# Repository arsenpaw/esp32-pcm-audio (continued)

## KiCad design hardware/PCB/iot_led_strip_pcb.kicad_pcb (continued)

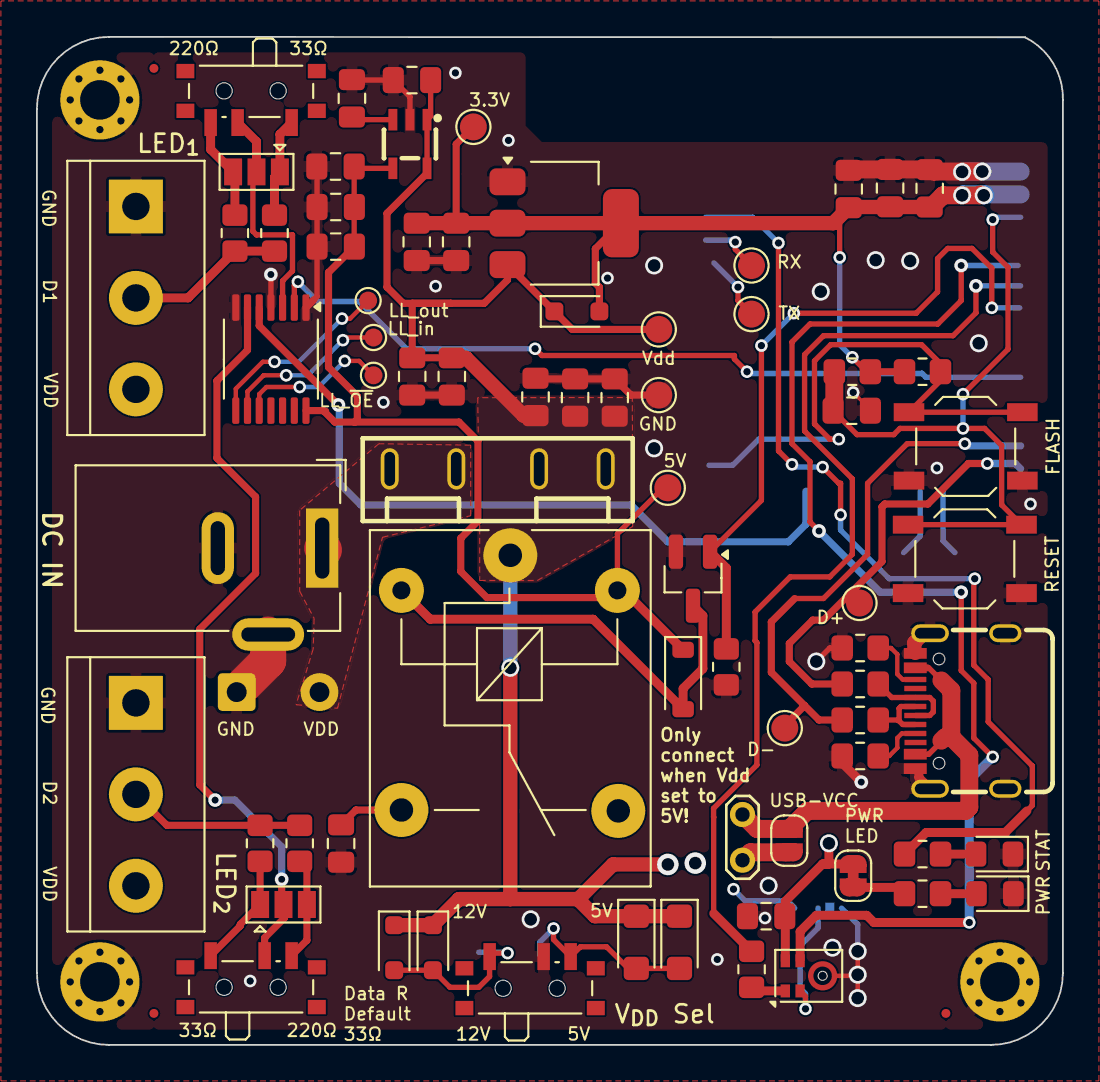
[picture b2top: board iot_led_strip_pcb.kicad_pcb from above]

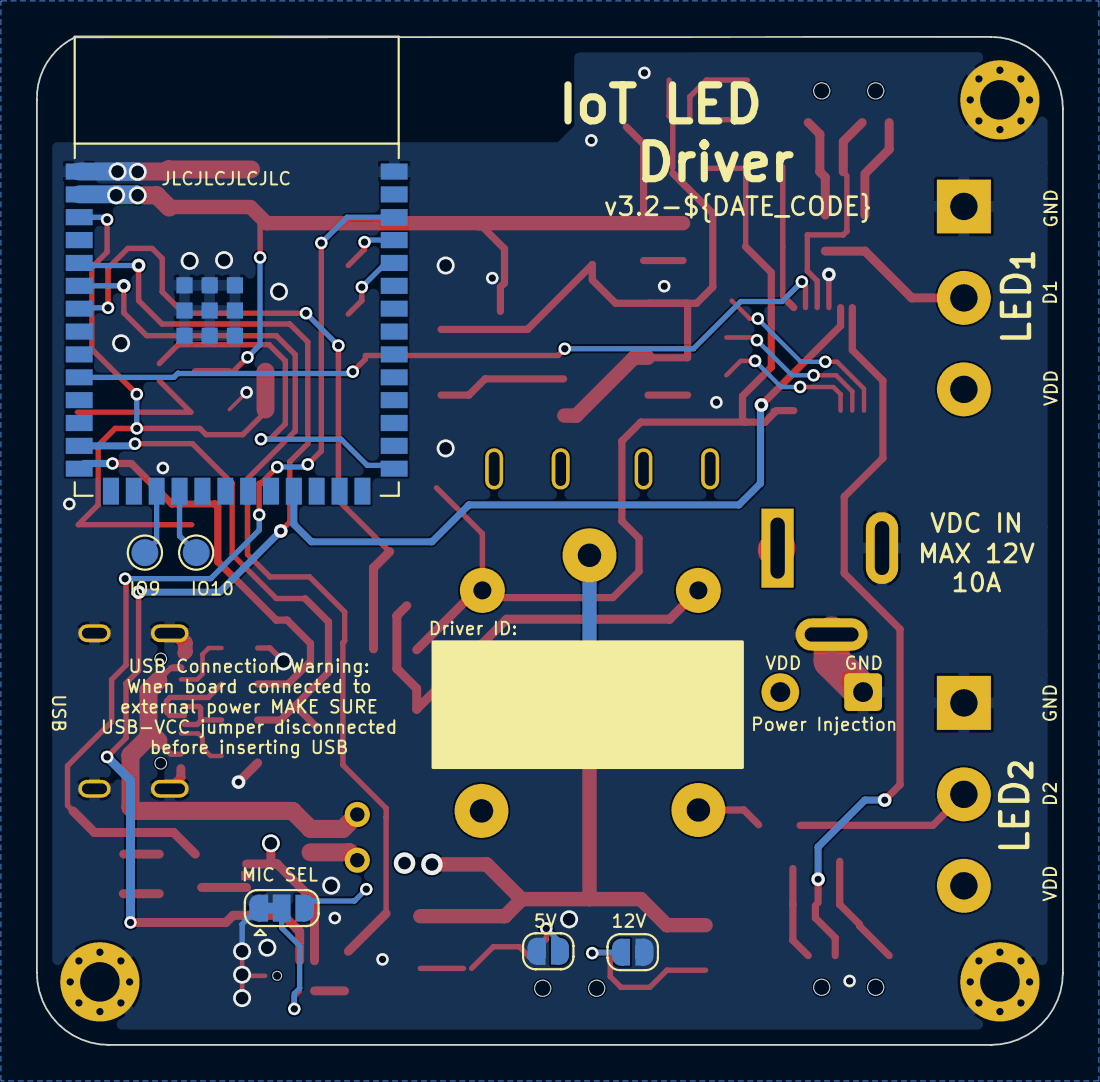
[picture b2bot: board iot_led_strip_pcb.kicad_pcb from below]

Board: 4 copper layers, 57.0 x 56.0 mm, 85 parts (6 on the bottom side), 45 nets.

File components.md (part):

# Components

This is everything you need to build **one** finished board, `hardware/PCB/iot_led_strip_pcb`,
including the parts that aren't soldered onto it. Part numbers are LCSC numbers, and each one
links to its LCSC page. Prices are in USD at qty 1.
- **Checked live on lcsc.com (2026-11-17/18):** U3, J3, and LCSC's lack of stock for MK1 and J4.
- **Everything else:** from the JLCPCB/LCSC parts snapshot dated 2026-11-14.

See [shop.md](shop.md) for why each part was chosen and for ways to cut cost.

## Decide first

The board has three spots where you either fit a switch to choose later or set the choice once
with a solder bridge. These choices change what you buy.

| Choice | Switchable (buy more) | Fixed (buy less) |
|---|---|---|
| **Strip voltage** (overvoltage protection) | Fit **SW5** ("Vdd Sel") and **both** TVS pairs, D1/D2 (5 V) and D7/D8 (12 V). | Skip SW5. Fit only **D1/D2** and bridge **JP4** for 5 V strips, or only **D7/D8** and bridge **JP8** for 12 V strips. JP4 and JP8 are on the back. |
| **Data-line resistor** per strip | Fit **SW3** and **SW4** and **all four** resistors: R7/R17 (33 Ω) and R16/R18 (220 Ω). | Skip SW3/SW4. Bridge JP5/JP6 toward the resistor you want. Fit only R7/R17 (33 Ω), when data and GND share a cable, or only R16/R18 (220 Ω), when they're separate wires. |
| **USB powers the board** | Fit the **JP1 header and jumper cap**, so you can pull the cap before connecting USB while external power is on. The board's back silkscreen warns about this. | Solder-bridge **JP3** instead. USB and the barrel jack are then always joined, so never plug in both. |

The tables below list the **switchable** version, which is everything.

## Parts soldered on the board

### Modules and ICs

| Ref | Qty | Part | What it does | LCSC | Unit $ |
|---|---|---|---|---|---|
| U3 | 1 | ESP32-S3-WROOM-1-N4 | Wi-Fi MCU that runs WLED. Use the S3, not the S2, so the PDM mic works. | [C2913197](https://www.lcsc.com/product-detail/C2913197.html) | 4.31 |
| MK1 | 1 | Knowles SPH0641LM4H-1 | PDM MEMS microphone for sound-reactive effects. **LCSC has none in stock.** Order it through JLCPCB assembly or from DigiKey/Mouser. SPH0641LU4H-1 also fits. | [C497724](https://www.lcsc.com/product-detail/C497724.html) | 1.68 |
| U4 | 1 | 74HCT125T14-13, TSSOP-14 | Shifts the 3.3 V data signal up to 5 V for the strips. | [C842453](https://www.lcsc.com/product-detail/C842453.html) | 0.24 |
| U1 | 1 | AMS1117-3.3, SOT-223 | 3.3 V regulator for the ESP32. | [C6186](https://www.lcsc.com/product-detail/C6186.html) | 0.21 |
| U2 | 1 | TAR5S50, SSOP-5 | 5 V regulator for the level shifter and relay coil, needed when running 12 V strips. | [C146354](https://www.lcsc.com/product-detail/C146354.html) | 0.36 |
| Q1 | 1 | AO3400A N-MOSFET, SOT-23 | Relay driver. | [C20917](https://www.lcsc.com/product-detail/C20917.html) | 0.09 |

### Connectors, relay and fuse holder

| Ref | Qty | Part | What it does | LCSC | Unit $ |
|---|---|---|---|---|---|
| J3 | 1 | G-Switch GT-USB-7010ASV, USB-C 16P | Programming and USB power. LCSC sells a minimum of 5. | [C2988369](https://www.lcsc.com/product-detail/C2988369.html) | 0.09 |
| J4 | 1 | **Würth 694106301002** DC barrel jack | Main power input. **Buy the genuine Würth part from DigiKey/Mouser.** LCSC only has DC005 lookalikes, rated 0.5–2 A, which may not fit this footprint. | — | — |
| J1, J2 | 2 | 3-pin 5.08 mm screw terminal | LED strip outputs (5V / DATA / GND). | [C500022](https://www.lcsc.com/product-detail/C500022.html) | 0.15 |
| K2 | 1 | Songle SRD-05VDC-SL-C relay | Lets WLED switch the strip power on and off. | [C35449](https://www.lcsc.com/product-detail/C35449.html) | 0.44 |
| F2 | 1 | XF-505P blade fuse holder, through-hole | Holds the main fuse, F3. | [C843270](https://www.lcsc.com/product-detail/C843270.html) | 0.11 |
| JP1 | 1 | 1×2 pin header, 2.54 mm | USB power link (see "Decide first"). | [C358684](https://www.lcsc.com/product-detail/C358684.html) | 0.01 |
| JP1 | 1 | Jumper cap, 2.54 mm | Fits the header above. | [C18185737](https://www.lcsc.com/product-detail/C18185737.html) | 0.01 |

### Switches

| Ref | Qty | Part | What it does | LCSC | Unit $ |
|---|---|---|---|---|---|
| SW1, SW2 | 2 | Tactile switch, 5.1 mm | RESET and FLASH (boot) buttons. | [C318884](https://www.lcsc.com/product-detail/C318884.html) | 0.02 |
| SW3, SW4 | 2 | SK-3296S-01-L1 slide switch | Picks the 33 Ω or 220 Ω data resistor for each strip. Optional. | [C319020](https://www.lcsc.com/product-detail/C319020.html) | 0.08 |
| SW5 | 1 | SK-3296S-01-L1 slide switch | Picks 5 V or 12 V strip protection. Optional. | [C319020](https://www.lcsc.com/product-detail/C319020.html) | 0.08 |

### Diodes and LEDs

| Ref | Qty | Part | What it does | LCSC | Unit $ |
|---|---|---|---|---|---|
| D1, D2 | 2 | SMF5.0A TVS, SMF | Overvoltage protection for **5 V** strips. Only 130 in stock; the fallback is [C1972946](https://www.lcsc.com/product-detail/C1972946.html) ($0.16). | [C20883238](https://www.lcsc.com/product-detail/C20883238.html) | 0.02 |
| D7, D8 | 2 | PTVSHC3D12VU TVS, SOD-323 | Overvoltage protection for **12 V** strips. | [C169336](https://www.lcsc.com/product-detail/C169336.html) | 0.04 |
| D3 | 1 | 1N5819WS Schottky, SOD-323 | Protects the 3.3 V regulator if its input drops below its output. | [C191023](https://www.lcsc.com/product-detail/C191023.html) | 0.01 |
| D6 | 1 | 1N4148W, SOD-123 | Flyback diode across the relay coil. | [C81598](https://www.lcsc.com/product-detail/C81598.html) | 0.01 |
| D4 | 1 | Green LED, 0805 | "STAT" status LED on GPIO2. | [C2297](https://www.lcsc.com/product-detail/C2297.html) | 0.02 |
| D5 | 1 | Red LED, 0805 | "PWR" power LED. You can disable it with JP2. | [C84256](https://www.lcsc.com/product-detail/C84256.html) | 0.01 |

### Capacitors (all 0805)

| Ref | Qty | Part | LCSC | Unit $ |
|---|---|---|---|---|
| C1-C3, C5, C8, C13, C15-C17 | 9 | 10 µF 25 V X5R | [C15850](https://www.lcsc.com/product-detail/C15850.html) | 0.07 |
| C4, C6, C7, C9-C12, C14, C18 | 9 | 100 nF 50 V X7R | [C49678](https://www.lcsc.com/product-detail/C49678.html) | 0.02 |

### Resistors (all 0805)

| Ref | Qty | Value | What it does | LCSC | Unit $ |
|---|---|---|---|---|---|
| R1, R4, R5 | 3 | 10 kΩ | Pull-ups and pull-downs. | [C17414](https://www.lcsc.com/product-detail/C17414.html) | 0.003 |
| R8, R9 | 2 | 5.1 kΩ | USB-C CC pins, so a USB-C charger supplies 5 V. | [C27834](https://www.lcsc.com/product-detail/C27834.html) | 0.006 |
| R12, R14 | 2 | 1 kΩ | LED current limiting. | [C17513](https://www.lcsc.com/product-detail/C17513.html) | 0.004 |
| R3, R10 | 2 | 27 Ω | USB data lines. | [C17594](https://www.lcsc.com/product-detail/C17594.html) | 0.003 |
| R6 | 1 | 100 Ω | Mic data line. | [C17408](https://www.lcsc.com/product-detail/C17408.html) | 0.004 |
| R7, R17 | 2 | 33 Ω | Strip data resistor, when data and GND share a cable. | [C17634](https://www.lcsc.com/product-detail/C17634.html) | 0.005 |
| R16, R18 | 2 | 220 Ω | Strip data resistor, when data and power run as separate wires. | [C17557](https://www.lcsc.com/product-detail/C17557.html) | 0.006 |

Not bought: JP2–JP8 are solder jumpers, and the TP test points, H mounting holes, FID fiducials
and J7 (power-injection wire pads) are bare copper.

## Parts not soldered on the board

| Item | Qty | Notes |
|---|---|---|
| **PCB** | 1 | `hardware/PCB/iot_led_strip_pcb.kicad_pcb`, about 57 × 56 mm. Order from JLCPCB or similar. |
| **F3 blade fuse** | 1 | A low-profile blade fuse to fit the XF-505P holder. Pick it for your strip current; the board is labelled max 10 A, and the holder is rated 15 A. |
| **Power supply** | 1 | 5 V or 12 V to match your strips, with a 5.5 × 2.1 mm barrel plug, sized for the strip current. A USB-C charger works for short strips. |
| **USB-C cable** | 1 | For flashing WLED. |
| **LED strips** | 1–2 | WS2812B (5 V) or WS2811 (12 V), connected to J1/J2 as 5V / DATA / GND. |
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
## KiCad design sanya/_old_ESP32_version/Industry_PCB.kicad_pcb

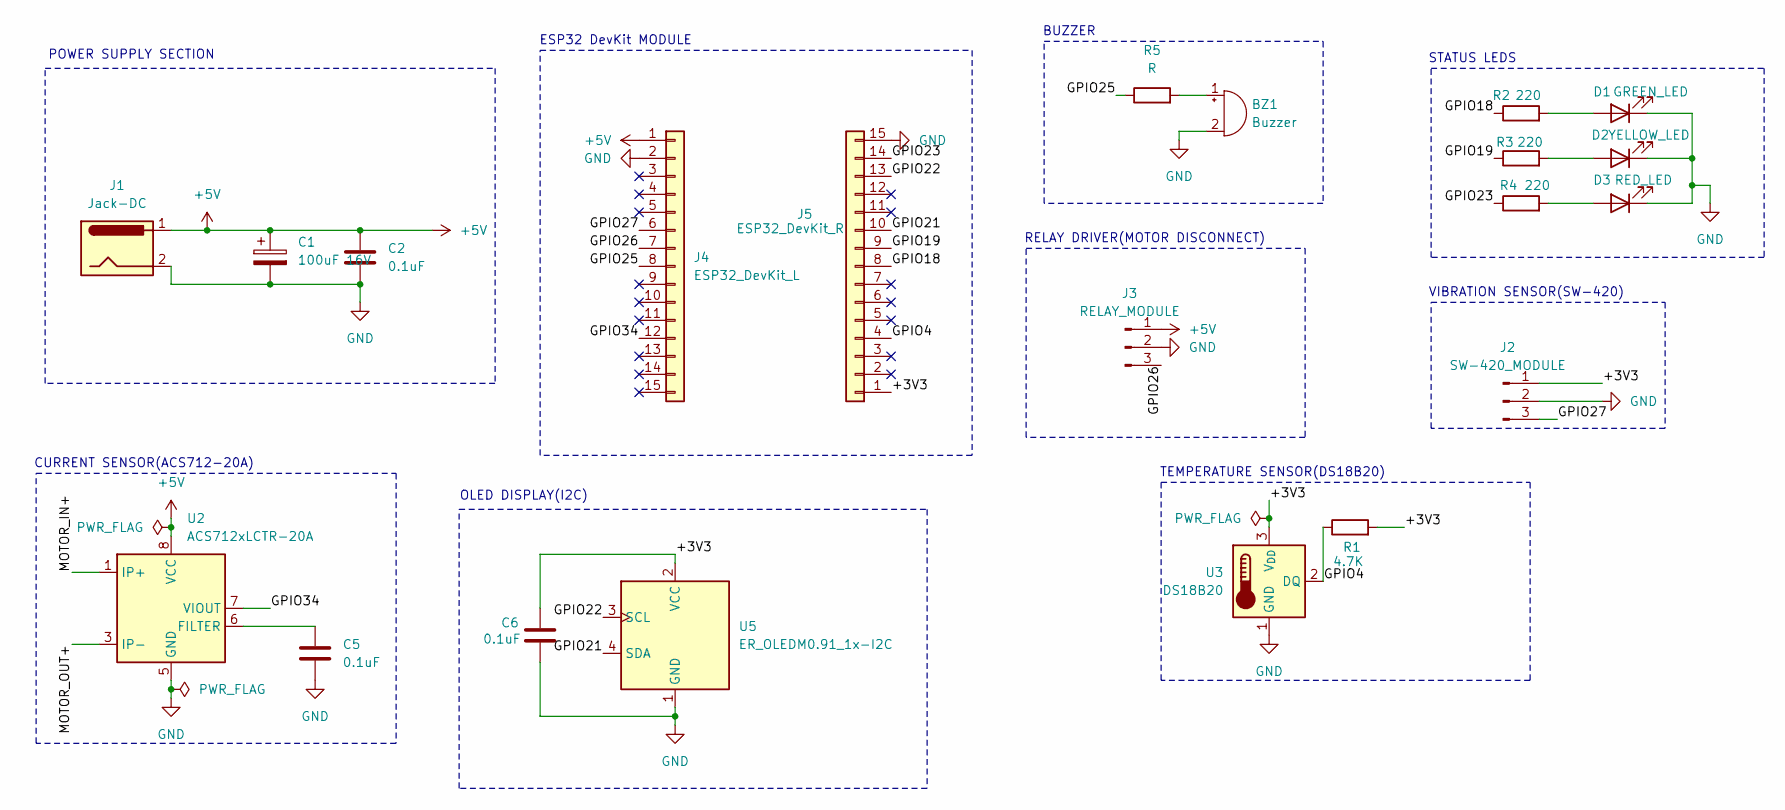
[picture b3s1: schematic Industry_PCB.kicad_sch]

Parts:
BZ1: Buzzer; Buzzer_12x9.5RM7.6
C1: 100uF 16V; CP_Radial_D6.3mm_P2.50mm
C2, C5, C6: 0.1uF; C_Disc_D5.1mm_W3.2mm_P5.00mm
D1: GREEN_LED; LED_D5.0mm
D2: YELLOW_LED; LED_D5.0mm
D3: RED_LED; LED_D5.0mm
J1: Jack-DC; BarrelJack_Horizontal
J2: SW-420_MODULE; PinHeader_1x03_P2.54mm_Vertical
J3: RELAY_MODULE; PinHeader_1x03_P2.54mm_Vertical
J4: ESP32_DevKit_L; PinHeader_1x15_P2.54mm_Vertical
J5: ESP32_DevKit_R; PinHeader_1x15_P2.54mm_Vertical
R1: 4.7K; R_Axial_DIN0207_L6.3mm_D2.5mm_P7.62mm_Horizontal
R2, R3, R4: 220; R_Axial_DIN0207_L6.3mm_D2.5mm_P7.62mm_Horizontal
R5: R; R_Axial_DIN0207_L6.3mm_D2.5mm_P7.62mm_Horizontal
U2: ACS712xLCTR-20A; SOIC-8_3.9x4.9mm_P1.27mm
U3: DS18B20; TO-92_Inline
U5: ER_OLEDM0.91_1x-I2C

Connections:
+5V: C1.1, C2.1, J1.1, J3.1, J4.1, U2.8 (VCC)
/+3V3: C6.1, J2.1, J5.1, R1.2, U3.3 (V_{DD}), U5.2 (VCC)
/GPIO4: J5.4, R1.1, U3.2 (DQ)
/GPIO18: J5.8, R2.1
/GPIO19: J5.9, R3.1
/GPIO21: J5.10, U5.4 (SDA)
/GPIO22: J5.13, U5.3 (SCL)
/GPIO23: J5.14, R4.1
/GPIO25: J4.8, R5.1
/GPIO26: J3.3, J4.7
/GPIO27: J2.3, J4.6
/GPIO34: J4.12, U2.7 (VIOUT)
/MOTOR_IN+: U2.1 (IP+), U2.2 (IP+)
/MOTOR_OUT+: U2.3 (IP-), U2.4 (IP-)
GND: BZ1.2 (-), C1.2, C2.2, C5.2, C6.2, D1.1 (K), D2.1 (K), D3.1 (K), J1.2, J2.2, J3.2, J4.2, J5.15, U2.5 (GND), U3.1 (GND), U5.1 (GND)
unnamed: BZ1.1 (+), R5.2
unnamed: D1.2 (A), R2.2
unnamed: D2.2 (A), R3.2
unnamed: D3.2 (A), R4.2
unnamed: C5.1, U2.6 (FILTER)

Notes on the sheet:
RELAY DRIVER(MOTOR DISCONNECT)
VIBRATION SENSOR(SW-420)
STATUS LEDS
ESP32 DevKit MODULE
TEMPERATURE SENSOR(DS18B20)
POWER SUPPLY SECTION
OLED DISPLAY(I2C)
CURRENT SENSOR(ACS712-20A)
BUZZER

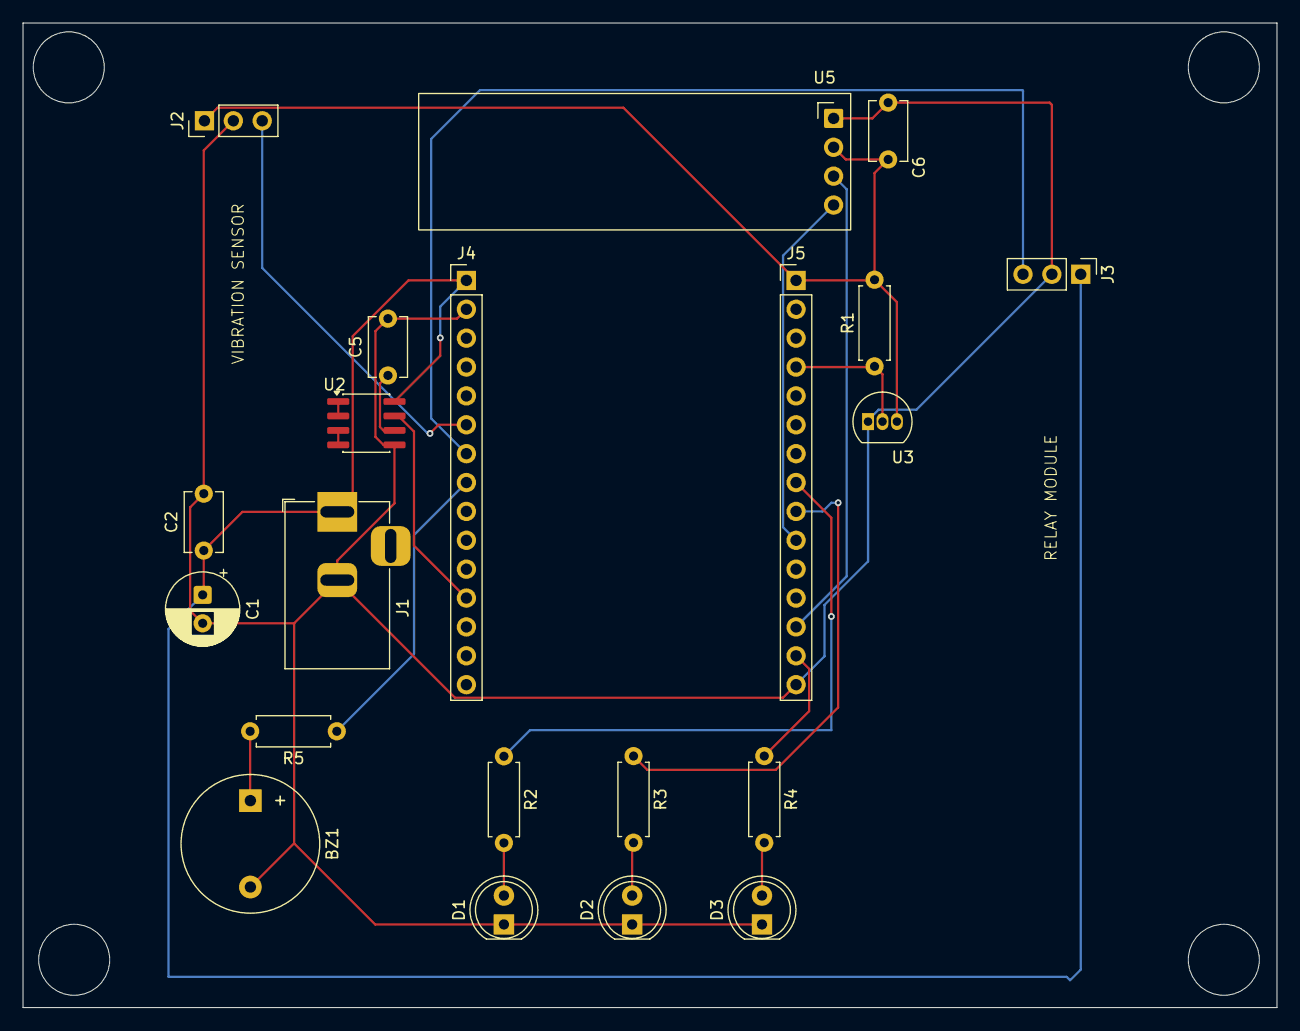
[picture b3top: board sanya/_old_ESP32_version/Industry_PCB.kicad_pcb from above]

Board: 2 copper layers, 110.3 x 86.6 mm, 21 parts (0 on the bottom side), 20 nets.

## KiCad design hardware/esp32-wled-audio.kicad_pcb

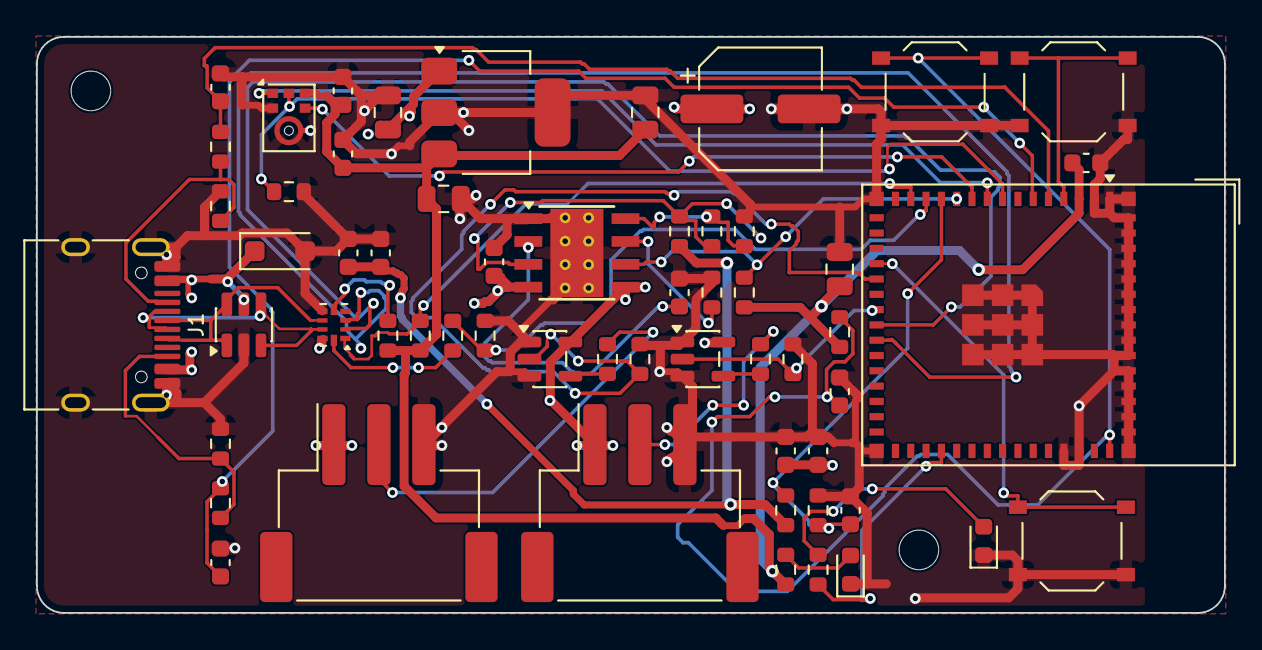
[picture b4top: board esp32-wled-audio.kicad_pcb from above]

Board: 4 copper layers, 66.0 x 32.0 mm, 60 parts (0 on the bottom side), 37 nets.

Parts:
C1: 47nF; C_0603_1608Metric
C2, C10, C12, C18: 1uF 16V; C_0603_1608Metric
C3: 470uF 10V; CP_Elec_6.3x7.7
C4, C5, C13: 10uF 16V; C_0805_2012Metric
C6: 22uF 10V; C_0805_2012Metric
C7, C8, C9, C11, C14, C15, C16, C17: 100nF; C_0603_1608Metric
D1: Red; LED_0603_1608Metric
D2: SMF5.0A; D_SOD-123F
D3: White; LED_0603_1608Metric
H1, H2: M2; MountingHole_2.2mm_M2
J1: TYPE-C-31-M-12; USB_C_Receptacle_HRO_TYPE-C-31-M-12
J2: STRIP1 5V/DATA/GND; JST_XH_S3B-XH-SM4-TB_1x03-1MP_P2.50mm_Horizontal
J3: STRIP2 5V/DATA/GND; JST_XH_S3B-XH-SM4-TB_1x03-1MP_P2.50mm_Horizontal
MK1: ICS-43434; InvenSense_ICS-43434-6_3.5x2.65mm
R1: 75k 1%; R_0603_1608Metric
R2: 6.04k 1%; R_0603_1608Metric
R3, R16: 20k 1%; R_0603_1608Metric
R4: 562R 1%; R_0603_1608Metric
R5, R11, R12, R13, R14, R17: 10k; R_0603_1608Metric
R6, R7: 100k 1%; R_0603_1608Metric
R8: 5.1k; R_0603_1608Metric
R9, R10: 5.1k 1%; R_0603_1608Metric
R15: 10k 1%; R_0603_1608Metric
R18: 1k; R_0603_1608Metric
R19, R20: 220R; R_0603_1608Metric
R21, R22, R23: 100k; R_0603_1608Metric
SW1: RESET; SW_Push_1P1T_XKB_TS-1187A
SW2: BOOT; SW_Push_1P1T_XKB_TS-1187A
SW3: USER; SW_Push_1P1T_XKB_TS-1187A
U1: TPS259630DDA; Texas_HSOP-8-1EP_3.9x4.9mm_P1.27mm_ThermalVias
U2: AP7361C-33E; SOT-223-3_TabPin2
U3: USBLC6-2SC6; SOT-23-6
U4: BQ24392RSER; Texas_R-PUQFN-N10
U5: ESP32-S3-MINI-1-N8; ESP32-S2-MINI-1
U6, U7: SN74LV1T125DBVR; SOT-23-5

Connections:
+3V3: C5.1, C6.1, C13.1, C14.1, C17.1, C18.1, MK1.5, R5.1, R8.1, R13.1, R14.1, R17.1, U2.3, U5.3
+5V_STRIP: C3.1, C15.1, C16.1, J2.1, J3.1, U1.5, U6.5, U7.5
BC_CHG_DET: R15.2, R16.1, U5.13
BC_CHG_DET_5V: R15.1, U4.10
BC_GOOD_BAT: R13.2, U4.5
BC_SW_OPEN: R14.2, U4.1, U5.14
BOOT: SW2.1, U5.4
CC1: J1.A5, R9.1, R11.1
CC1_SENSE: C8.1, R11.2, U5.5
CC2: J1.B5, R10.1, R12.1
CC2_SENSE: C9.1, R12.2, U5.6
EFUSE_DVDT: C1.1, U1.2
EFUSE_EN: R1.2, R2.1, U1.3
EFUSE_FLT: R5.2, U1.6, U5.11
EFUSE_ILM: R4.1, U1.7
EFUSE_OVLO: R2.2, R3.1, U1.8
EN: C12.1, R17.2, SW1.1, U5.45
GND: C1.2, C2.2, C3.2, C4.2, C5.2, C6.2, C7.2, C8.2, C9.2, C10.2, C11.2, C12.2, C13.2, C14.2, C15.2, C16.2, C17.2, C18.2, D1.1, D2.2, D3.1, J1.A1, J1.A12, J1.B1, J1.B12, J1.SH, J2.3, J3.3, MK1.2, MK1.3, R3.2, R4.2, R7.2, R9.2, R10.2, R16.2, R21.2, R22.2, R23.2, SW1.2, SW2.2, SW3.2, U1.1, U1.9, U2.2, U3.2, U4.6, U5.1, U5.2, U5.42, U5.43, U5.46, U5.47, U5.48, U5.49, U5.50, U5.51, U5.52, U5.53, U5.54, U5.55, U5.56, U5.57, U5.58, U5.59, U5.60, U5.61, U5.62, U5.63, U5.64, U5.65, U6.1, U6.3, U7.1, U7.3
I2S_SCK: MK1.4, U5.10
I2S_SD: MK1.6, R23.1, U5.8
I2S_WS: MK1.1, U5.9
LED1_DATA: J2.2, R19.2
LED1_DATA_3V3: R21.1, U5.20, U6.2
LED1_DATA_5V: R19.1, U6.4
LED2_DATA: J3.2, R20.2
LED2_DATA_3V3: R22.1, U5.22, U7.2
LED2_DATA_5V: R20.1, U7.4
PWR_LED_A: D1.2, R8.2
STATUS_LED: R18.1, U5.34
STAT_LED_A: D3.2, R18.2
USB_CON_DM: J1.A7, J1.B7, U3.3, U3.4, U4.8
USB_CON_DP: J1.A6, J1.B6, U3.1, U3.6, U4.7
USB_DM: U4.2, U5.23
USB_DP: U4.3, U5.24
USER_BTN: SW3.1, U5.19
VBUS: C2.1, C4.1, C10.1, C11.1, D2.1, J1.A4, J1.A9, J1.B4, J1.B9, R1.1, R6.1, U1.4, U2.1, U3.5, U4.9
VBUS_SENSE: C7.1, R6.2, R7.1, U5.12
